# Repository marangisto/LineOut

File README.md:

# LineOut
Passive Modular Line Output

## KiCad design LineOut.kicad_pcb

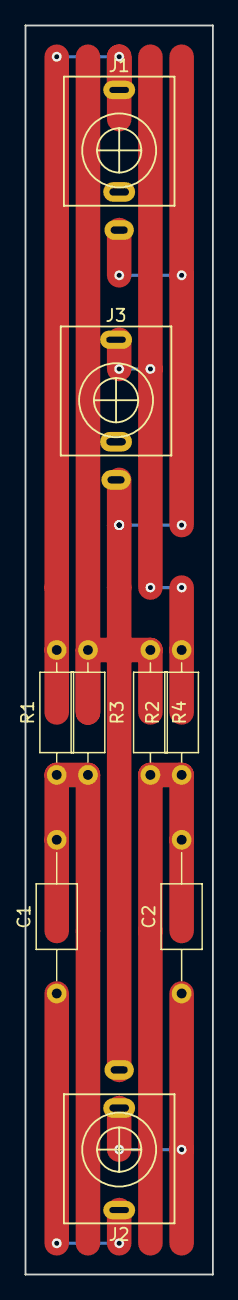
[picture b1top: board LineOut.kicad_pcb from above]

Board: 2 copper layers, 15.2 x 101.6 mm, 9 parts (0 on the bottom side), 7 nets.

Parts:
C1, C2: 1u; C_Axial_L5.1mm_D3.1mm_P12.50mm_Horizontal
J1, J3: AudioJack2_SwitchT; PJ398SM
J2: AudioJack3; PJ366ST
R1, R3: 10k; R_Axial_DIN0207_L6.3mm_D2.5mm_P10.16mm_Horizontal
R2, R4: 1k; R_Axial_DIN0207_L6.3mm_D2.5mm_P10.16mm_Horizontal

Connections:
GND: J1.S, J1.TN, J2.S, J3.S, J3.TN, R2.1, R4.1
unnamed: C1.1, J2.T
unnamed: C1.2, R1.1, R2.2
unnamed: C2.1, J2.R
unnamed: C2.2, R3.1, R4.2
unnamed: J1.T, R1.2
unnamed: J3.T, R3.2

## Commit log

2018-08-08 Added audio jack footprints.
2018-08-08 Line Out schematic and strip-board PCB.
2018-12-31 Upgraded to KiCad 5.02.
